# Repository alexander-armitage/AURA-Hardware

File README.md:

<div align="center">

# AURA
### Autonomous Universal Robotics Architecture

</div>

## Contents

1. [Overview](#overview)  
2. [Repository Structure](#repository-structure)
3. [License](#license)

## Overview

AURA (Autonomous Universal Robotics Architecture) is a modular set of PCBs designed for robotics applications. This repository includes schematics, layouts, and KiCad project files to facilitate prototyping and production.

The software framework to run on this hardware can be seen in another repository [here](https://github.com/alexander-armitage/AURA-Software).

### Features
#### MCU
- Dual Core 240MHz ESP32-S3
- Onboard IMU (ICM20948) 
- Onboard barometer (BMP280)
- Flash storage (128 MBit)
- SD card support
- 1x CAN connector
- 1x I2C connector
- 2x SPI connector
- 2x UART connectors
- 12x PWM output channels
- Power switching
- ESD protection

#### PDB
- 1x Battery pass-through
- 1x 5V 20A continuous output
- 2x high-current (10A) output channels
- 2S-6S LiPo battery input support
- Reverse polarity protection
- Power, Current, and Voltage sensing
- ESD protection

## Repository Structure

```
AURA-Hardware/
├── .github/              # Images for README
├── MCU_AURA/             # ESP32S3 based PCB project
│ ├── Gerber/             # Manufacturing files (JLCPCB)
│ ├── Libraries/          # Local project libraries
| ├── Pick_n_Place/       # Files to generate pick and place (JLCPCB)
│ └── MCU_AURA.kicad_pro  # Project file for KiCad
├── PDB_AURA/             # Power distribution board PCB project
│ ├── Gerber/             # Manufacturing files (JLCPCB)
│ ├── Libraries/          # Local project libraries
| ├── Pick_n_Place/       # Files to generate pick and place (JLCPCB)
│ └── PDB_AURA.kicad_pro  # Project file for KiCad
├── docs/                 # Schematics for the PCB projects
├── .gitignore            # Git ignore file
├── README.md             # Project overview
└── LICENSE               # License file
```

## License
See the [LICENSE](./LICENSE) file for more details.

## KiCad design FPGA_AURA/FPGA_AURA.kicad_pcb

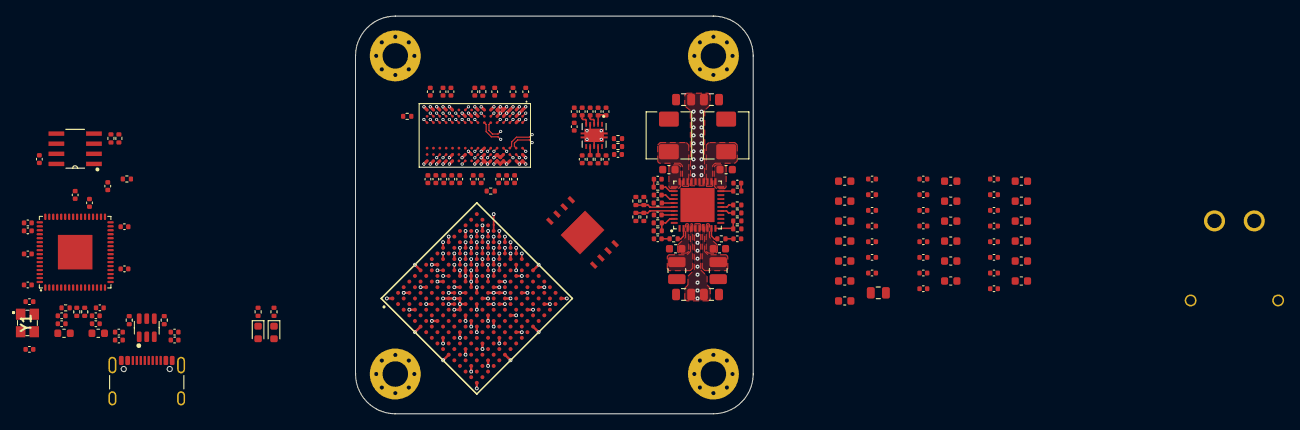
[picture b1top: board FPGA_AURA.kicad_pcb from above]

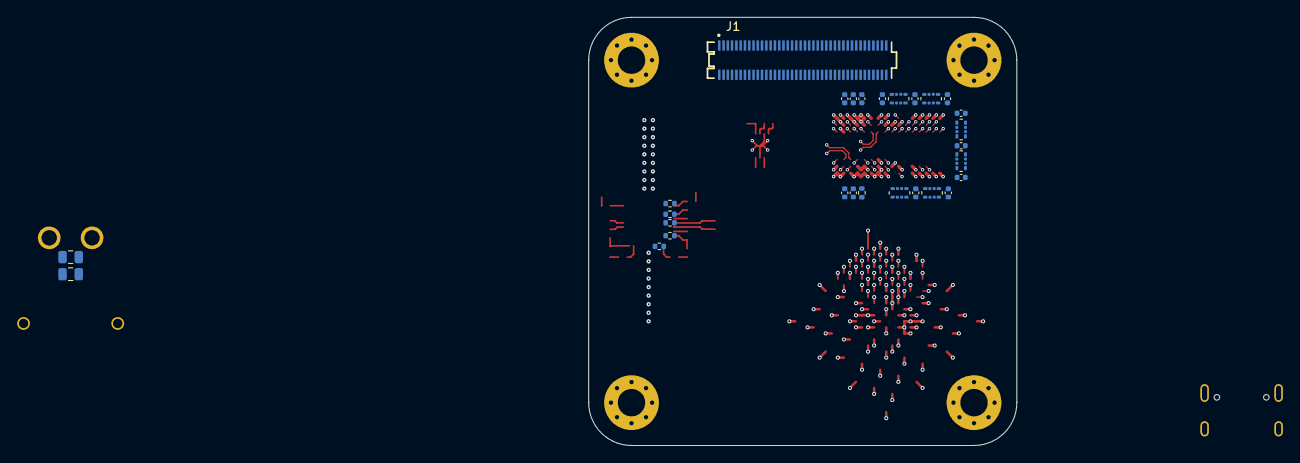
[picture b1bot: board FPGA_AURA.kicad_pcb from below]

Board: 8 copper layers, 50.0 x 50.0 mm, 187 parts (28 on the bottom side), 111 nets.

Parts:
C1, C3, C4, C5, C6, C7, C8, C9, C10, C12, C14, C17, C102, C103, C214, C500, C501, C502, C503, C504, C505, C506, C507, C512, C513, C514, C515, C516, C517, C518, C519, C520, C521, C522, C523, C524, C525, C526, C527, C528, C529, C530, C531: 100n; C_0402_1005Metric
C2, C11, C13, C221: 4u7; C_0402_1005Metric
C15, C16: 27pF; C_0402_1005Metric
C18: 100u; C_0805_2012Metric
C19, C20, C21, C22, C24, C34, C35, C41, C42, C48, C49, C55, C56: 4u7; C_0603_1608Metric
C23, C26, C27, C28, C29, C30, C31, C36, C37, C38, C39, C43, C44, C45, C46, C50, C51, C52, C53, C57, C58, C59, C60, C205: 470n; C_0402_1005Metric
C25, C32, C33, C40, C47, C54: 47; C_0603_1608Metric
C100, C101, C206, C207, C208, C209: 47u; C_0805_2012Metric
C104, C105, C220: 1u; C_0402_1005Metric
C200, C201, C202, C203: 10u; C_0603_1608Metric
C210: 3n6; C_0402_1005Metric
C211: 8n; C_0402_1005Metric
C212: 2n2; C_0402_1005Metric
C213: 5n; C_0402_1005Metric
C215, C217, C218, C219, C222, C508: 10u; C_0402_1005Metric
C216: 1n; C_0402_1005Metric
C510, C511: 10n; C_0402_1005Metric
D105, D106: LED; LED_0603_1608Metric
FB1, FB2: 120R; L_0603_1608Metric
H100, H101, H102, H103: MountingHole_Pad; MountingHole_3.2mm_M3_Pad_Via
J1: ST5-40-1.00-L-D-P-TR
J100: USB_C_Receptacle_USB2.0_16P; USB_C_Receptacle_GCT_USB4105-xx-A_16P_TopMnt_Horizontal
J101: XT30PW-M; XT30PWM
L200: 680n; L_Chilisin_BMRB00050518-B
L201: 1u; L_Chilisin_BMRB00050518-B
L202: 1u5; L_1008_2520Metric
L203: 2u2; L_1008_2520Metric
R1: 10R; R_0402_1005Metric
R2, R3: 22R; R_0402_1005Metric
R4, R108, R109, R209: 1k; R_0402_1005Metric
R5, R6: 12k; R_0402_1005Metric
R100, R101: 5k1; R_0402_1005Metric
R200: 27k; R_0402_1005Metric
R201: 4k9; R_0402_1005Metric
R202, R204: 0R; R_0402_1005Metric
R203: 56k2; R_0402_1005Metric
R205: 31k6; R_0402_1005Metric
R206: 100k; R_0402_1005Metric
R207, R208, R210, R211, R213, R220, R221, R222, R223, R524: 10k; R_0402_1005Metric
R212: 22k; R_0402_1005Metric
R214: 15k; R_0402_1005Metric
R215, R216: 2k7; R_0402_1005Metric
R217: 5k6; R_0402_1005Metric
R218: 9k1; R_0402_1005Metric
R219: 47k; R_0402_1005Metric
R508, R509, R510, R511, R512, R513: 0402_4
R522: 81R; R_0402_1005Metric
R523: 240R; R_0402_1005Metric
R525: 40R; R_0402_1005Metric
U1: XC7A35T-2FTG256C; BGA256C100P16X16_1700X1700X155
U2: W25Q256JVEIQ; SON127P800X600X80-9N
U3: FT2232HQ; QFN50P900X900X100-65N
U4: TPS51200DRCR; VREG_V62_16624-01YE
U5: USBLC6-2SC6; SOT-23-6
U6: 93LC56BT-I_SN; SOIC127P600X175-8N
U200: ADP5014; QFN50P600X600X80-41N430X430
U500: MT41K128M16JT-125_IT_K; BGA80P96C6X16_800X1400X110
Y1: 12MHz; X322512MSB4SI

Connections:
+1V0: C18.1, C19.1, C20.1, C21.1, C23.1, C26.1, C27.1, C28.1, C206.1, L200.2, U1.E10 (VCCBRAM), U1.F7 (VCCINT), U1.F9 (VCCINT), U1.F11 (VCCBRAM), U1.G6 (VCCINT), U1.H9 (VCCINT), U1.J6 (VCCINT), U1.K9 (VCCINT), U1.L8 (VCCINT), U200.33 (FB1)
+1V8: C22.1, C24.1, C25.1, C29.1, C30.1, C31.1, C207.1, L201.2, U1.G8 (VCCADC_0), U1.G10 (VCCAUX), U1.J10 (VCCAUX), U1.K11 (VCCAUX), U1.L10 (VCCAUX), U200.18 (FB2)
+1V8_FTDI: C2.1, C8.1, C9.1, C10.1, U3.12 (VCORE), U3.37 (VCORE), U3.49 (VREGOUT), U3.64 (VCORE)
+1V35: C40.1, C41.1, C42.1, C43.1, C44.1, C45.1, C46.1, C208.1, C217.1, C218.1, C511.1, C512.1, C513.1, C514.1, C515.1, C516.1, C517.1, C518.1, C519.1, C520.1, C521.1, C522.1, C523.1, C524.1, C525.1, C526.1, C527.1, C528.1, C529.1, C530.1, C531.1, L202.2, R222.1, U1.A16 (VCCO_15), U1.B13 (VCCO_15), U1.C10 (VCCO_15), U1.E14 (VCCO_15), U1.H15 (VCCO_15), U1.J12 (VCCO_15), U4.2 (VLDOIN), U200.1 (FB3), U500.A1 (VDDQ), U500.A8 (VDDQ), U500.B2 (VDD), U500.C1 (VDDQ), U500.C9 (VDDQ), U500.D2 (VDDQ), U500.D9 (VDD), U500.E9 (VDDQ), U500.F1 (VDDQ), U500.G7 (VDD), U500.H2 (VDDQ), U500.H9 (VDDQ), U500.K2 (VDD), U500.K8 (VDD), U500.N1 (VDD), U500.N9 (VDD), U500.R1 (VDD), U500.R9 (VDD)
+3V3: C1.1, C3.1, C4.1, C5.1, C6.1, C7.1, C17.1, C32.1, C33.1, C34.1, C35.1, C36.1, C37.1, C38.1, C39.1, C47.1, C48.1, C49.1, C50.1, C51.1, C52.1, C53.1, C54.1, C55.1, C56.1, C57.1, C58.1, C59.1, C60.1, C209.1, C221.1, FB1.1, FB2.1, L203.2, R5.1, R213.1, R219.1, R220.1, R223.1, U1.A6 (VCCO_35), U1.B3 (VCCO_35), U1.D7 (VCCO_35), U1.E4 (VCCO_35), U1.F1 (VCCO_35), U1.J2 (VCCO_35), U1.L6 (VCCO_0), U1.L16 (VCCO_14), U1.M3 (VCCO_34), U1.M13 (VCCO_14), U1.N10 (VCCO_14), U1.P7 (VCCO_14), U1.R4 (VCCO_34), U1.R14 (VCCO_14), U1.T1 (VCCO_34), U1.T11 (VCCO_14), U2.8 (VCC), U3.20 (VCCIO), U3.31 (VCCIO), U3.42 (VCCIO), U3.50 (VREGIN), U3.56 (VCCIO), U4.10 (VIN), U6.8 (VCC)
+5V: C100.1, C101.1, C200.1, C201.1, C202.1, C203.1, C220.1, D106.2 (A), J101.1, R200.1, U200.3 (PVIN3), U200.8 (PVIN4), U200.17 (EN1/ENALL), U200.20 (PVIN2), U200.21 (PVIN2), U200.30 (PVIN1), U200.31 (PVIN1), U200.34 (AVIN)
+5V_USB: C102.1, C103.1, C104.1, C105.1, D105.2 (A), J100.A4 (VBUS), J100.A9 (VBUS), J100.B4 (VBUS), J100.B9 (VBUS), U5.5 (VBUS)
+VREF: C205.1, C214.1, C510.1, C511.2, R207.1, R209.1, R211.1, U4.6 (REFOUT), U200.38 (VREF), U200.40 (VSET4), U500.H1 (VREFDQ), U500.M8 (VREFCA)
+VTT: C215.1, C219.1, C222.1, C500.1, C501.1, C502.1, C503.1, C504.1, C505.1, C506.1, C507.1, C508.1, R508.1, R508.3, R508.5, R508.7, R509.1, R509.3, R509.5, R509.7, R510.1, R510.3, R510.5, R510.7, R511.1, R511.3, R511.5, R511.7, R512.1, R512.3, R512.5, R512.7, R513.3, R513.5, R525.1, U4.3 (VO), U4.5 (VOSNS)
/100_Power_Switching/5V_LED: D106.1 (K), R109.2
/100_Power_Switching/USB_CC1: J100.A5 (CC1), R101.2
/100_Power_Switching/USB_CC2: J100.B5 (CC2), R100.2
/100_Power_Switching/USB_LED: D105.1 (K), R108.2
/200_Power_Regulation/ADP_1V0_PD: R207.2, R208.1, U200.36 (VSET1)
/200_Power_Regulation/ADP_1V8_PD: R209.2, R210.1, U200.37 (VSET2)
/200_Power_Regulation/ADP_1V35_PD: R211.2, R212.1, U200.39 (VSET3)
/200_Power_Regulation/ADP_CFG1: R204.1, U200.15 (CFG1)
/200_Power_Regulation/ADP_CFG2: R205.1, U200.14 (CFG2)
/200_Power_Regulation/ADP_COMP1: R215.1, U200.32 (COMP1)
/200_Power_Regulation/ADP_COMP2: R216.1, U200.19 (COMP2)
/200_Power_Regulation/ADP_COMP3: R217.1, U200.2 (COMP3)
/200_Power_Regulation/ADP_COMP4: R218.1, U200.9 (COMP4)
/200_Power_Regulation/ADP_EN2: R202.2, U200.16 (EN2/DL12)
/200_Power_Regulation/ADP_EN4: R203.2, U200.12 (EN4/DL34)
/200_Power_Regulation/ADP_FB4: R213.2, R214.1, U200.10 (FB4)
/200_Power_Regulation/ADP_RC1: C210.1, R215.2
/200_Power_Regulation/ADP_RC2: C211.1, R216.2
/200_Power_Regulation/ADP_RC3: C212.1, R217.2
/200_Power_Regulation/ADP_RC4: C213.1, R218.2
/200_Power_Regulation/ADP_RT: R206.1, U200.35 (RT)
/200_Power_Regulation/ADP_SW1: L200.1, U200.28 (SW1), U200.29 (SW1)
/200_Power_Regulation/ADP_SW2: L201.1, U200.22 (SW2), U200.23 (SW2)
/200_Power_Regulation/ADP_SW3: L202.1, U200.4 (SW3)
/200_Power_Regulation/ADP_SW4: L203.1, U200.7 (SW4)
/200_Power_Regulation/ADP_UV: R200.2, R201.1, U200.13 (EN3/UV)
/200_Power_Regulation/TPS_REFIN: C216.1, R221.1, R222.2, U4.1 (REFIN)
/400_FPGA_Config/FTDI_EECLK: U3.62 (EECLK), U6.2 (CLK)
/400_FPGA_Config/FTDI_EECS: U3.63 (EECS), U6.1 (CS)
/400_FPGA_Config/FTDI_EEDI: R4.2, U3.61 (EEDATA), U6.3 (DI)
/400_FPGA_Config/FTDI_EEDO: R4.1, R5.2, U6.4 (DO)
/400_FPGA_Config/FTDI_REF: R6.1, U3.6 (REF)
/400_FPGA_Config/OSCI_FTDI: C15.1, U3.2 (OSCI), Y1.1
/400_FPGA_Config/OSCO_FTDI: C16.1, U3.3 (OSCO), Y1.3
/400_FPGA_Config/QSPI_CLK: R1.2, U2.6 (CLK)
/400_FPGA_Config/QSPI_CLK_R: R1.1, U1.E8 (CCLK_0)
/400_FPGA_Config/QSPI_CS#: U1.L12 (IO_L6P_T0_FCS_B_14), U2.1 (/CS)
/400_FPGA_Config/QSPI_IO0: U1.J13 (IO_L1P_T0_D00_MOSI_14), U2.5 (DI_IO0)
/400_FPGA_Config/QSPI_IO1: U1.J14 (IO_L1N_T0_D01_DIN_14), U2.2 (DO_IO1)
/400_FPGA_Config/QSPI_IO2: U1.K15 (IO_L2P_T0_D02_14), U2.3 (/WP_IO2)
/400_FPGA_Config/QSPI_IO3: U1.K16 (IO_L2N_T0_D03_14), U2.7 (/HOLD_IO3)
/400_FPGA_Config/USB_FPGA_D+: R2.1, U5.4 (I/O2)
/400_FPGA_Config/USB_FPGA_D-: R3.1, U5.6 (I/O1)
/400_FPGA_Config/USB_R_D+: R2.2, U3.8 (DP)
/400_FPGA_Config/USB_R_D-: R3.2, U3.7 (DM)
/400_FPGA_Config/VPHY_FTDI: C13.1, C14.1, FB2.2, U3.4 (VPHY)
/400_FPGA_Config/VPLL_FTDI: C11.1, C12.1, FB1.2, U3.9 (VPLL)
/500_DDR3L/DDR3_ZQ: R523.1, U500.L8 (ZQ)
ADP_UVO_LED: R219.2, U200.11 (GPIO)
DDR3_A0: R509.8, U1.B11 (IO_L4N_T0_15), U500.N3 (A0)
DDR3_A1: R509.6, U1.B16 (IO_L10N_T1_AD11N_15), U500.P7 (A1)
DDR3_A2: R509.4, U1.C13 (IO_L12N_T1_MRCC_15), U500.P3 (A2)
DDR3_A3: R509.2, U1.B12 (IO_L5P_T0_AD9P_15), U500.N2 (A3)
DDR3_A4: R508.8, U1.B10 (IO_L4P_T0_15), U500.P8 (A4)
DDR3_A5: R508.6, U1.D8 (IO_L6P_T0_15), U500.P2 (A5)
DDR3_A6: R508.4, U1.C9 (IO_L1N_T0_AD0N_15), U500.R8 (A6)
DDR3_A7: R508.2, U1.C8 (IO_L1P_T0_AD0P_15), U500.R2 (A7)
DDR3_A8: R512.8, U1.A9 (IO_L2N_T0_AD8N_15), U500.T8 (A8)
DDR3_A9: R512.6, U1.D9 (IO_L6N_T0_VREF_15), U500.R3 (A9)
DDR3_A10: R512.4, U1.A14 (IO_L7N_T1_AD2N_15), U500.L7 (A10/AP)
DDR3_A11: R512.2, U1.A8 (IO_L2P_T0_AD8P_15), U500.R7 (A11)
DDR3_A12: R513.6, U1.A15 (IO_L9N_T1_DQS_AD3N_15), U500.N7 (A12/~BC)
DDR3_A13: R513.4, U1.D10 (IO_0_15), U500.T3 (A13)
DDR3_BA0: R510.2, U1.C12 (IO_L11N_T1_SRCC_15), U500.M2 (BA0)
DDR3_BA1: R510.4, U1.A12 (IO_L5N_T0_AD9N_15), U500.N8 (BA1)
DDR3_BA2: R510.6, U1.A13 (IO_L7P_T1_AD2P_15), U500.M3 (BA2)
DDR3_CAS: R511.6, U1.B14 (IO_L8N_T1_AD10N_15), U500.K3 (~CAS)
DDR3_CK+: R522.1, U1.B9 (IO_L3P_T0_DQS_AD1P_15), U500.J7 (CK)
DDR3_CK-: R522.2, U1.A10 (IO_L3N_T0_DQS_AD1N_15), U500.K7 (~CK)
DDR3_CKE: R510.8, U1.C11 (IO_L11P_T1_SRCC_15), U500.K9 (CKE)
DDR3_CS: R511.2, U1.B15 (IO_L9P_T1_DQS_AD3P_15), U500.L2 (~CS)
DDR3_DM0: U1.E13 (IO_L13N_T2_MRCC_15), U500.E7 (LDM)
DDR3_DM1: U1.H11 (IO_L19P_T3_A22_15), U500.D3 (UDM)
DDR3_DQ0: U1.E11 (IO_L14P_T2_SRCC_15), U500.E3 (DQ0)
DDR3_DQ1: U1.D11 (IO_L14N_T2_SRCC_15), U500.F7 (DQ1)
DDR3_DQ2: U1.F12 (IO_L16P_T2_A28_15), U500.F2 (DQ2)
DDR3_DQ3: U1.D16 (IO_L17N_T2_A25_15), U500.F8 (DQ3)
DDR3_DQ4: U1.F15 (IO_L18P_T2_A24_15), U500.H3 (DQ4)
DDR3_DQ5: U1.E15 (IO_L18N_T2_A23_15), U500.H8 (DQ5)
DDR3_DQ6: U1.F13 (IO_L16N_T2_A27_15), U500.G2 (DQ6)
DDR3_DQ7: U1.E16 (IO_L17P_T2_A26_15), U500.H7 (DQ7)
DDR3_DQ8: U1.H13 (IO_L20N_T3_A19_15), U500.A7 (DQ12)
DDR3_DQ9: U1.G15 (IO_L24N_T3_RS0_15), U500.C3 (DQ9)
DDR3_DQ10: U1.G12 (IO_L19N_T3_A21_VREF_15), U500.C8 (DQ10)
DDR3_DQ11: U1.H12 (IO_L20P_T3_A20_15), U500.D7 (DQ8)
DDR3_DQ12: U1.J16 (IO_L23N_T3_FWE_B_15), U500.C2 (DQ11)
DDR3_DQ13: U1.J15 (IO_L23P_T3_FOE_B_15), U500.A2 (DQ13)
DDR3_DQ14: U1.G16 (IO_L22N_T3_A16_15), U500.B8 (DQ14)
DDR3_DQ15: U1.H16 (IO_L22P_T3_A17_15), U500.A3 (DQ15)
DDR3_DQS0+: U1.D14 (IO_L15P_T2_DQS_15), U500.F3 (LDQS)
DDR3_DQS0-: U1.D15 (IO_L15N_T2_DQS_ADV_B_15), U500.G3 (~LDQS)
DDR3_DQS1+: U1.G14 (IO_L21P_T3_DQS_15), U500.C7 (UDQS)
DDR3_DQS1-: U1.F14 (IO_L21N_T3_DQS_A18_15), U500.B7 (~UDQS)
DDR3_ODT: R525.2, U1.C16 (IO_L10P_T1_AD11P_15), U500.K1 (ODT)
DDR3_RAS: R511.4, U1.C14 (IO_L8P_T1_AD10P_15), U500.J3 (~RAS)
DDR3_RESET: R524.1, U1.E12 (IO_L13P_T2_MRCC_15), U500.T2 (~RESET)
DDR3_WE: R511.8, U1.D13 (IO_L12P_T1_MRCC_15), U500.L3 (~WE)
DDR_PGOOD: R223.2, U4.9 (PGOOD)
GND: C1.2, C2.2, C3.2, C4.2, C5.2, C6.2, C7.2, C8.2, C9.2, C10.2, C11.2, C12.2, C13.2, C14.2, C15.2, C16.2, C17.2, C18.2, C19.2, C20.2, C21.2, C22.2, C23.2, C24.2, C25.2, C26.2, C27.2, C28.2, C29.2, C30.2, C31.2, C32.2, C33.2, C34.2, C35.2, C36.2, C37.2, C38.2, C39.2, C40.2, C41.2, C42.2, C43.2, C44.2, C45.2, C46.2, C47.2, C48.2, C49.2, C50.2, C51.2, C52.2, C53.2, C54.2, C55.2, C56.2, C57.2, C58.2, C59.2, C60.2, C100.2, C101.2, C102.2, C103.2, C104.2, C105.2, C200.2, C201.2, C202.2, C203.2, C205.2, C206.2, C207.2, C208.2, C209.2, C210.2, C211.2, C212.2, C213.2, C214.2, C215.2, C216.2, C217.2, C218.2, C219.2, C220.2, C221.2, C222.2, C500.2, C501.2, C502.2, C503.2, C504.2, C505.2, C506.2, C507.2, C508.2, C510.2, C512.2, C513.2, C514.2, C515.2, C516.2, C517.2, C518.2, C519.2, C520.2, C521.2, C522.2, C523.2, C524.2, C525.2, C526.2, C527.2, C528.2, C529.2, C530.2, C531.2, H100.1 (1_1), H101.1 (1_1), H102.1 (1_1), H103.1 (1_1), J100.A1 (GND), J100.A12 (GND), J100.B1 (GND), J100.B12 (GND), J101.2, J101.3, J101.4, R6.2, R100.1, R101.1, R108.1, R109.1, R201.2, R202.1, R203.1, R204.2, R205.2, R206.2, R208.2, R210.2, R212.2, R214.2, R221.2, R523.2, R524.2, U1.A1 (GND), U1.A11 (GND), U1.B8 (GND), U1.C5 (GND), U1.C15 (GND), U1.D2 (GND), U1.D12 (GND), U1.E9 (GND), U1.F6 (GND), U1.F8 (VCCBATT_0), U1.F10 (GND), U1.F16 (GND), U1.G3 (GND), U1.G7 (GNDADC_0), U1.G9 (GND), U1.G13 (GND), U1.H6 (GND), U1.H7 (VREFN_0), U1.J8 (VREFP_0), U1.J9 (GND), U1.J11 (GND), U1.K4 (GND), U1.K6 (GND), U1.K14 (GND), U1.L1 (GND), U1.L11 (GND), U1.M8 (GND), U1.N5 (GND), U1.N15 (GND), U1.P2 (GND), U1.P12 (GND), U1.R9 (GND), U1.T6 (GND), U1.T16 (GND), U2.4 (GND), U2.9 (EXP), U3.1 (GND), U3.5 (GND), U3.10 (AGND), U3.11 (GND), U3.13 (TEST), U3.15 (GND), U3.25 (GND), U3.35 (GND), U3.47 (GND), U3.51 (GND), U3.65 (GND), U4.4 (PGND), U4.8 (GND), U4.11 (EPAD), U5.2 (GND), U6.5 (VSS), U200.5 (PGND3), U200.6 (PGND4), U200.24 (PGND2), U200.25 (PGND2), U200.26 (PGND1), U200.27 (PGND1), U200.41 (EP), U500.A9 (VSS), U500.B1 (VSSQ), U500.B3 (VSS), U500.B9 (VSSQ), U500.D1 (VSSQ), U500.D8 (VSSQ), U500.E1 (VSS), U500.E2 (VSSQ), U500.E8 (VSSQ), U500.F9 (VSSQ), U500.G1 (VSSQ), U500.G8 (VSS), U500.G9 (VSSQ), U500.J2 (VSS), U500.J8 (VSS), U500.M1 (VSS), U500.M9 (VSS), U500.P1 (VSS), U500.P9 (VSS), U500.T1 (VSS), U500.T9 (VSS), Y1.2, Y1.4
unnamed: R220.2, U4.7 (EN)
USB_D+: J100.A6 (D+), J100.B6 (D+), U5.3 (I/O2)
USB_D-: J100.A7 (D-), J100.B7 (D-), U5.1 (I/O1)

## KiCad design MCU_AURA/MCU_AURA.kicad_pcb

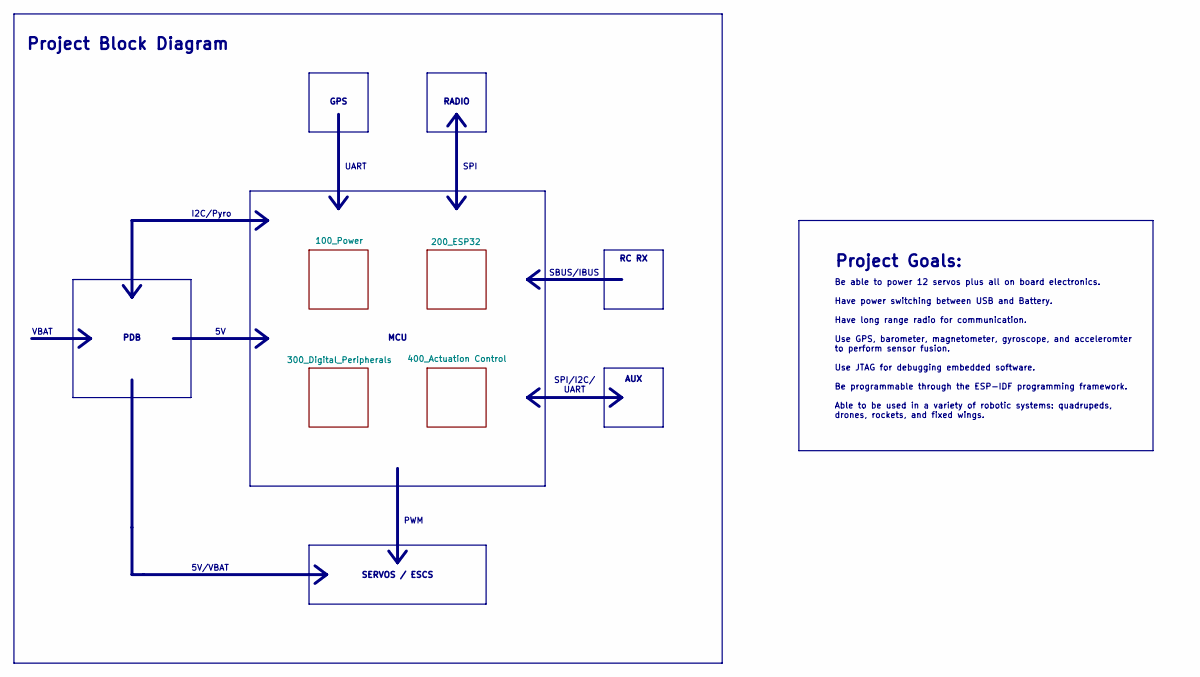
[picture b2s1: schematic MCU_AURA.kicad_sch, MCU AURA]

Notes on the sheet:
GPS
SPI
SPI/I2C/ UART
UART
Be able to power 12 servos plus all on board electronics. Have power switching between USB and Battery. Have long range radio for communication. Use GPS, barometer, magnetometer, gyroscope, and acceleromter to perform sensor fusion. Use JTAG for debugging embedded software. Be programmable through 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
SBUS/IBUS
RADIO
PDB
I2C/Pyro
Project Block Diagram
MCU
Project Goals:
5V/VBAT
PWM
VBAT
AUX
RC RX
SERVOS / ESCS

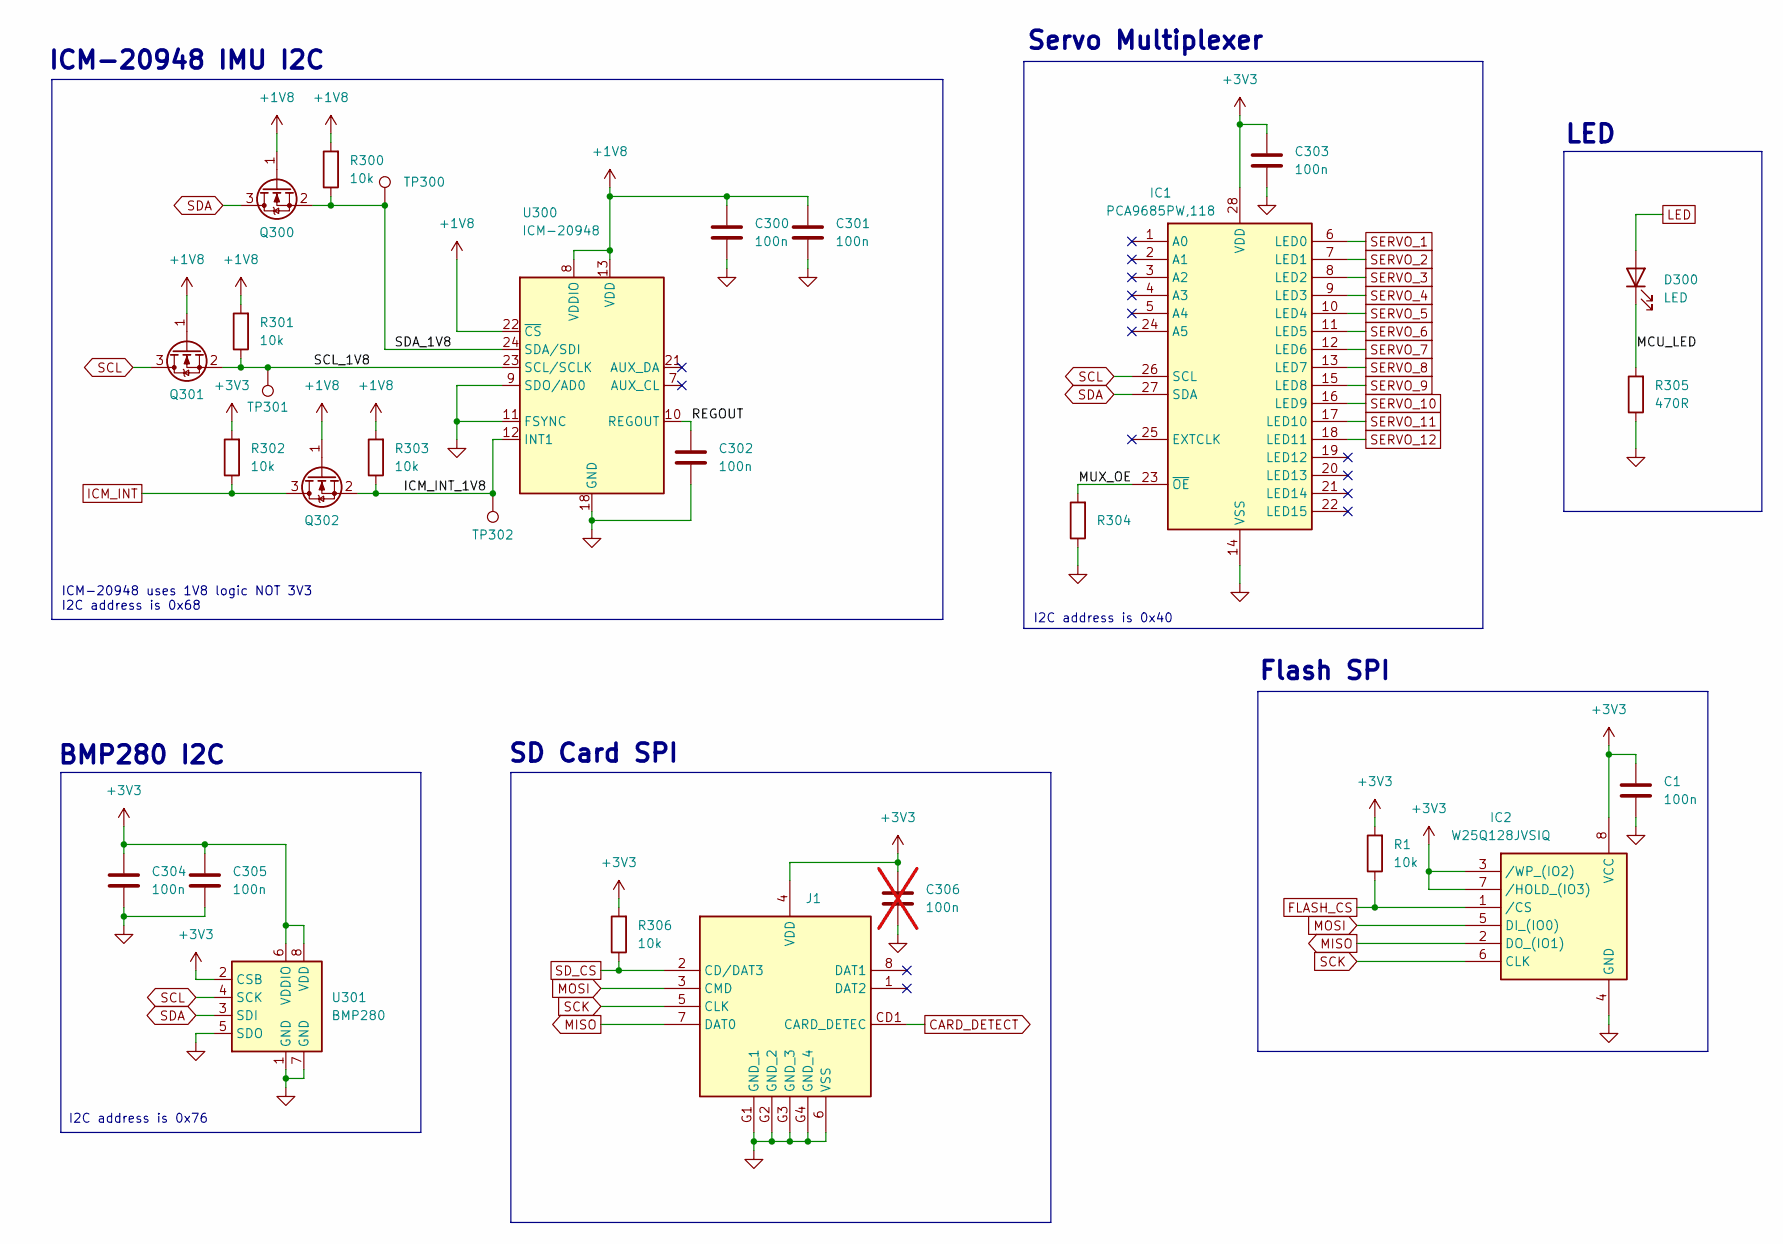
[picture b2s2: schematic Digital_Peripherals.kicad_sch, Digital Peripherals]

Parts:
C1, C300, C301, C302, C303, C304, C305: 100n; C_0402_1005Metric
C306: 100n; C_0402_1005Metric; not fitted
D300: LED; LED_0603_1608Metric
IC1: PCA9685PW,118; SOP65P640X110-28N; Manufacturer_Part_Number PCA9685PW,118; Mouser Part Number 771-PCA9685PW,118
IC2: W25Q128JVSIQ; SOIC127P790X216-8N; Manufacturer_Part_Number W25Q128JVSIQ; Mouser Part Number 454-W25Q128JVSIQ
J1: TF-CARD_H1.8; TFCARDH18; Manufacturer_Part_Number TF-CARD H1.8
Q300, Q301, Q302: BSS138; SOT-23
R1, R300, R301, R302, R303, R304, R306: 10k; R_0402_1005Metric
R305: 470R; R_0402_1005Metric
TP300, TP301, TP302: TestPoint; TestPoint_Pad_D1.0mm
U300: ICM-20948; InvenSense_QFN-24_3x3mm_P0.4mm
U301: BMP280; Bosch_LGA-8_2x2.5mm_P0.65mm_ClockwisePinNumbering

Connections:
+1V8: C300.1, C301.1, Q300.1 (G), Q301.1 (G), Q302.1 (G), R300.2, R301.2, R303.2, U300.8 (VDDIO), U300.13 (VDD), U300.22 (~CS); also elsewhere on the board
+3V3: C1.1, C303.1, C304.1, C305.1, C306.1, IC1.28 (VDD), IC2.3 (/WP_(IO2)), IC2.7 (/HOLD_(IO3)), IC2.8 (VCC), J1.4 (VDD), R1.2, R302.2, R306.2, U301.2 (CSB), U301.6 (VDDIO), U301.8 (VDD); also elsewhere on the board
/300_Digital_Peripherals/ICM_INT_1V8: Q302.2 (S), R303.1, TP302.1, U300.12 (INT1)
/300_Digital_Peripherals/MCU_LED: D300.1 (K), R305.2
/300_Digital_Peripherals/MUX_OE: IC1.23 (~OE), R304.2
/300_Digital_Peripherals/REGOUT: C302.1, U300.10 (REGOUT)
/300_Digital_Peripherals/SCL_1V8: Q301.2 (S), R301.1, TP301.1, U300.23 (SCL/SCLK)
/300_Digital_Peripherals/SDA_1V8: Q300.2 (S), R300.1, TP300.1, U300.24 (SDA/SDI)
CARD_DETECT: J1.CD1 (CARD_DETEC); also elsewhere on the board
FLASH_CS: IC2.1 (/CS), R1.1; also elsewhere on the board
GND: C1.2, C300.2, C301.2, C302.2, C303.2, C304.2, C305.2, C306.2, IC1.14 (VSS), IC2.4 (GND), J1.6 (VSS), J1.G1 (GND_1), J1.G2 (GND_2), J1.G3 (GND_3), J1.G4 (GND_4), R304.1, R305.1, U300.9 (SDO/AD0), U300.11 (FSYNC), U300.18 (GND), U300.20 (GND), U301.1 (GND), U301.5 (SDO), U301.7 (GND); also elsewhere on the board
ICM_INT: Q302.3 (D), R302.1; also elsewhere on the board
LED: D300.2 (A); also elsewhere on the board
MISO: IC2.2 (DO_(IO1)), J1.7 (DAT0); also elsewhere on the board
MOSI: IC2.5 (DI_(IO0)), J1.3 (CMD); also elsewhere on the board
SCK: IC2.6 (CLK), J1.5 (CLK); also elsewhere on the board
SCL: IC1.26 (SCL), Q301.3 (D), U301.4 (SCK); also elsewhere on the board
SDA: IC1.27 (SDA), Q300.3 (D), U301.3 (SDI); also elsewhere on the board
SD_CS: J1.2 (CD/DAT3), R306.1; also elsewhere on the board
SERVO_1: IC1.6 (LED0); also elsewhere on the board
SERVO_2: IC1.7 (LED1); also elsewhere on the board
SERVO_3: IC1.8 (LED2); also elsewhere on the board
SERVO_4: IC1.9 (LED3); also elsewhere on the board
SERVO_5: IC1.10 (LED4); also elsewhere on the board
SERVO_6: IC1.11 (LED5); also elsewhere on the board
SERVO_7: IC1.12 (LED6); also elsewhere on the board
SERVO_8: IC1.13 (LED7); also elsewhere on the board
SERVO_9: IC1.15 (LED8); also elsewhere on the board
SERVO_10: IC1.16 (LED9); also elsewhere on the board
SERVO_11: IC1.17 (LED10); also elsewhere on the board
SERVO_12: IC1.18 (LED11); also elsewhere on the board

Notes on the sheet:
Flash SPI
I2C address is 0x40
I2C address is 0x76
BMP280 I2C
SD Card SPI
ICM-20948 IMU I2C
Servo Multiplexer
ICM-20948 uses 1V8 logic NOT 3V3 I2C address is 0x68
LED

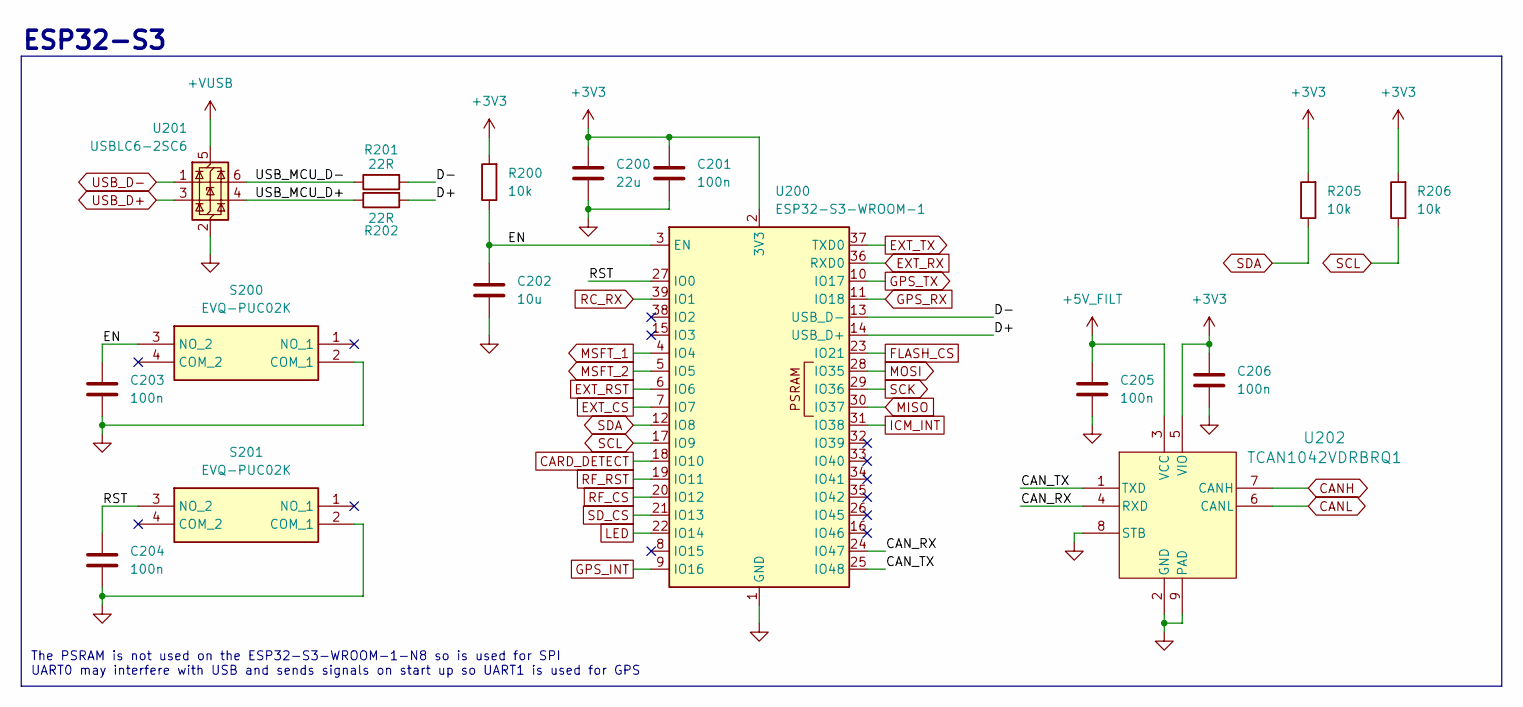
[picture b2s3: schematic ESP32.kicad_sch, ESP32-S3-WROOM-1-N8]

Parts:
C200: 22u; C_0402_1005Metric
C201, C203, C204, C205, C206: 100n; C_0402_1005Metric
C202: 10u; C_0402_1005Metric
R200, R205, R206: 10k; R_0402_1005Metric
R201, R202: 22R; R_0402_1005Metric
S200, S201: EVQ-PUC02K; EVQPUC02K; Manufacturer_Part_Number EVQ-PUC02K; Mouser Part Number 667-EVQ-PUC02K
U200: ESP32-S3-WROOM-1
U201: USBLC6-2SC6; SOT-23-6
U202: TCAN1042VDRBRQ1; DRB0008F

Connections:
+3V3: C200.1, C201.1, C206.1, R200.2, R205.2, R206.2, U200.2 (3V3), U202.5 (VIO); also elsewhere on the board
+5V_FILT: C205.1, U202.3 (VCC); also elsewhere on the board
+VUSB: U201.5 (VBUS); also elsewhere on the board
/200_ESP32/CAN_RX: U200.24 (IO47), U202.4 (RXD)
/200_ESP32/CAN_TX: U200.25 (IO48), U202.1 (TXD)
/200_ESP32/D+: R202.2, U200.14 (USB_D+)
/200_ESP32/D-: R201.2, U200.13 (USB_D-)
/200_ESP32/EN: C202.1, C203.1, R200.1, S200.3 (NO_2), U200.3 (EN)
/200_ESP32/RST: C204.1, S201.3 (NO_2), U200.27 (IO0)
/200_ESP32/USB_MCU_D+: R202.1, U201.4 (I/O2)
/200_ESP32/USB_MCU_D-: R201.1, U201.6 (I/O1)
CANH: U202.7 (CANH); also elsewhere on the board
CANL: U202.6 (CANL); also elsewhere on the board
CARD_DETECT: U200.18 (IO10); also elsewhere on the board
EXT_CS: U200.7 (IO7); also elsewhere on the board
EXT_RST: U200.6 (IO6); also elsewhere on the board
EXT_RX: U200.36 (RXD0); also elsewhere on the board
EXT_TX: U200.37 (TXD0); also elsewhere on the board
FLASH_CS: U200.23 (IO21); also elsewhere on the board
GND: C200.2, C201.2, C202.2, C203.2, C204.2, C205.2, C206.2, S200.2 (COM_1), S201.2 (COM_1), U200.1 (GND), U200.40 (GND), U200.41 (GND), U201.2 (GND), U202.2 (GND), U202.8 (STB), U202.9 (PAD); also elsewhere on the board
GPS_INT: U200.9 (IO16); also elsewhere on the board
GPS_RX: U200.11 (IO18); also elsewhere on the board
GPS_TX: U200.10 (IO17); also elsewhere on the board
ICM_INT: U200.31 (IO38); also elsewhere on the board
LED: U200.22 (IO14); also elsewhere on the board
MISO: U200.30 (IO37); also elsewhere on the board
MOSI: U200.28 (IO35); also elsewhere on the board
MSFT_1: U200.4 (IO4); also elsewhere on the board
MSFT_2: U200.5 (IO5); also elsewhere on the board
RC_RX: U200.39 (IO1); also elsewhere on the board
RF_CS: U200.20 (IO12); also elsewhere on the board
RF_RST: U200.19 (IO11); also elsewhere on the board
SCK: U200.29 (IO36); also elsewhere on the board
SCL: R206.1, U200.17 (IO9); also elsewhere on the board
SDA: R205.1, U200.12 (IO8); also elsewhere on the board
SD_CS: U200.21 (IO13); also elsewhere on the board
USB_D+: U201.3 (I/O2); also elsewhere on the board
USB_D-: U201.1 (I/O1); also elsewhere on the board

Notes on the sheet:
The PSRAM is not used on the ESP32-S3-WROOM-1-N8 so is used for SPI UART0 may interfere with USB and sends signals on start up so UART1 is used for GPS
ESP32-S3

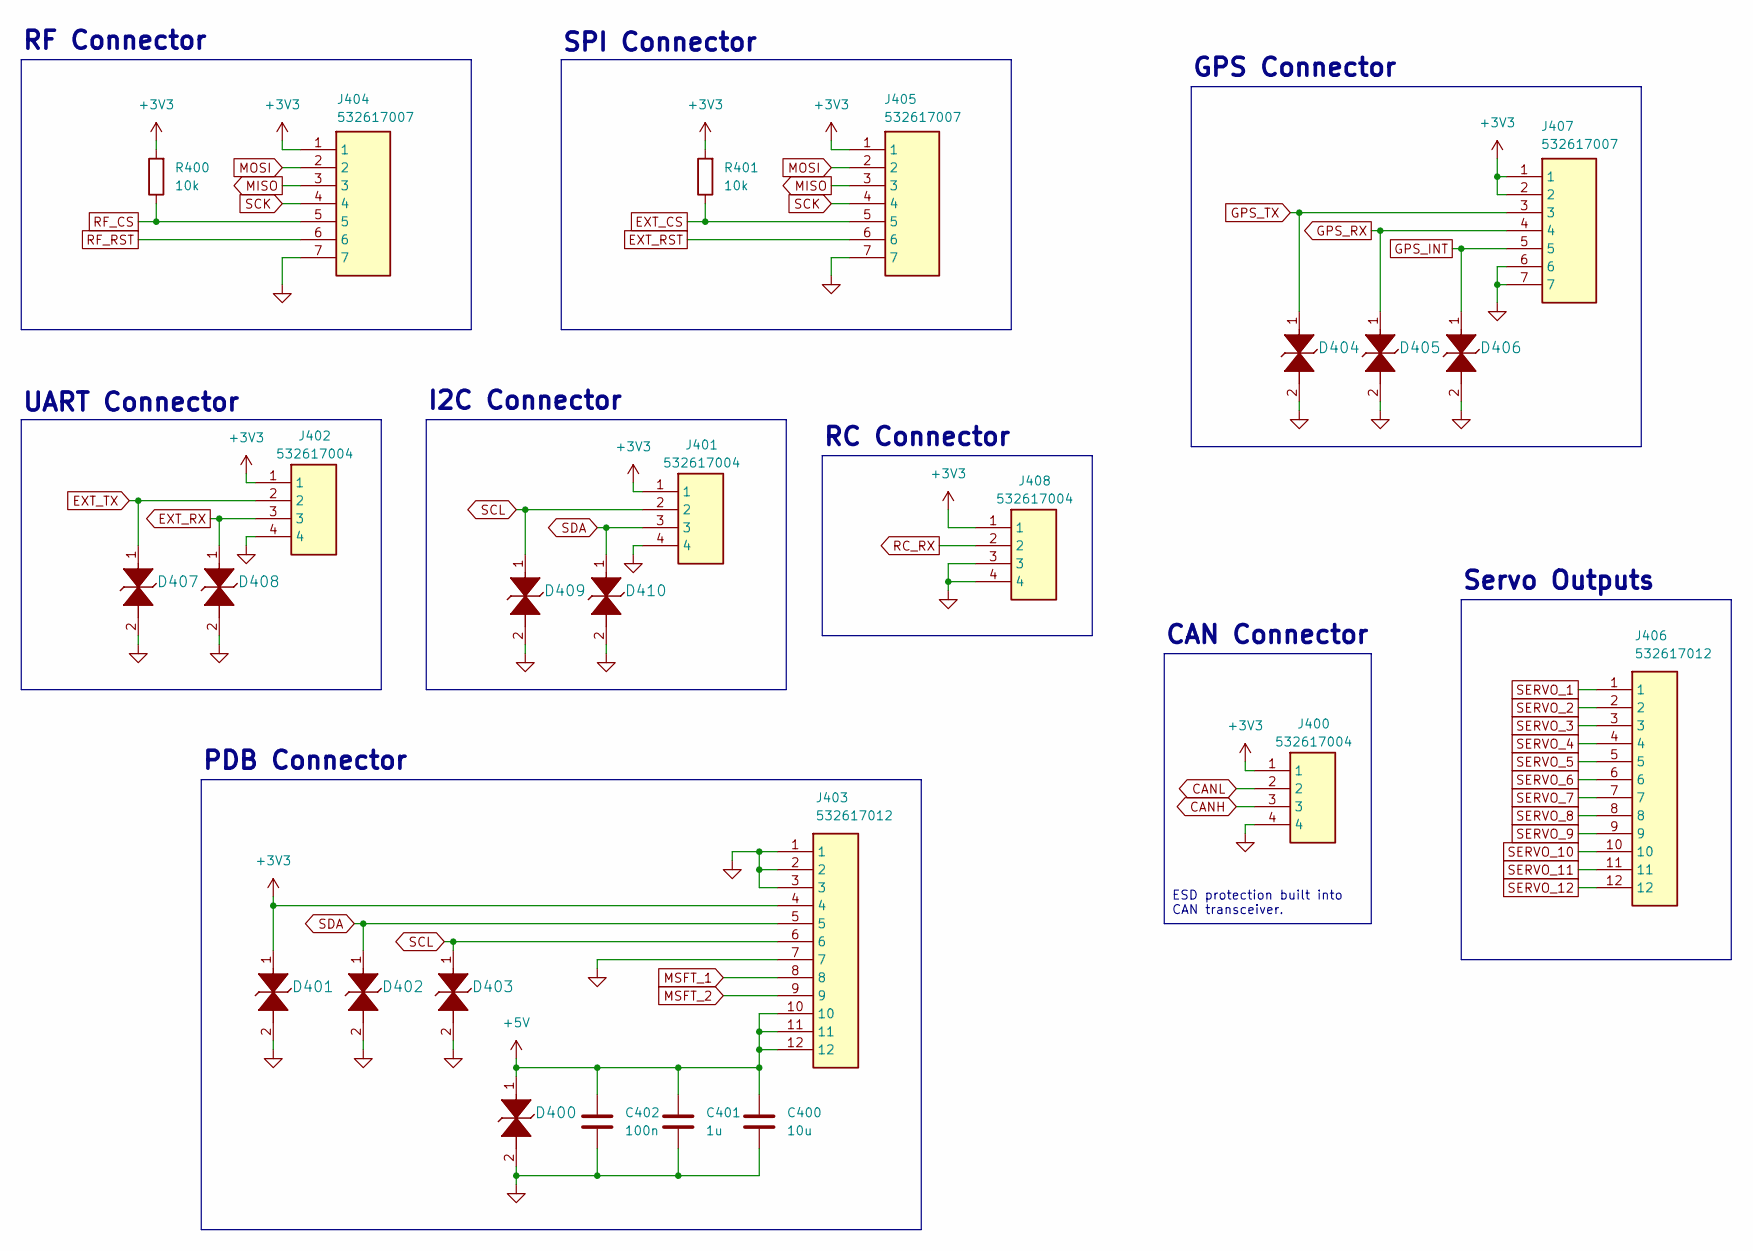
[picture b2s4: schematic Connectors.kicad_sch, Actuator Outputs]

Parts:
C400: 10u; C_0402_1005Metric
C401: 1u; C_0402_1005Metric
C402: 100n; C_0402_1005Metric
D400, D401, D402, D403, D404, D405, D406, D407, D408, D409, D410: TPD1E05U06DPYR; DIO_TPD1E05U06DPYR
J400, J401, J402, J408: 532617004; 53261-0471; Manufacturer_Part_Number 532617004
J403, J406: 532617012; 53261-1271; Manufacturer_Part_Number 532617012
J404, J405, J407: 532617007; 532610771; Manufacturer_Part_Number 532617007
R400, R401: 10k; R_0402_1005Metric

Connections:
+3V3: D401.1, J400.1, J401.1, J402.1, J403.4, J404.1, J405.1, J407.1, J407.2, J408.1, R400.2, R401.2; also elsewhere on the board
+5V: C400.1, C401.1, C402.1, D400.1, J403.10, J403.11, J403.12; also elsewhere on the board
CANH: J400.3; also elsewhere on the board
CANL: J400.2; also elsewhere on the board
EXT_CS: J405.5, R401.1; also elsewhere on the board
EXT_RST: J405.6; also elsewhere on the board
EXT_RX: D408.1, J402.3; also elsewhere on the board
EXT_TX: D407.1, J402.2; also elsewhere on the board
GND: C400.2, C401.2, C402.2, D400.2, D401.2, D402.2, D403.2, D404.2, D405.2, D406.2, D407.2, D408.2, D409.2, D410.2, J400.4, J401.4, J402.4, J403.1, J403.2, J403.3, J403.7, J404.7, J405.7, J407.6, J407.7, J408.3, J408.4; also elsewhere on the board
GPS_INT: D406.1, J407.5; also elsewhere on the board
GPS_RX: D405.1, J407.4; also elsewhere on the board
GPS_TX: D404.1, J407.3; also elsewhere on the board
MISO: J404.3, J405.3; also elsewhere on the board
MOSI: J404.2, J405.2; also elsewhere on the board
MSFT_1: J403.8; also elsewhere on the board
MSFT_2: J403.9; also elsewhere on the board
RC_RX: J408.2; also elsewhere on the board
RF_CS: J404.5, R400.1; also elsewhere on the board
RF_RST: J404.6; also elsewhere on the board
SCK: J404.4, J405.4; also elsewhere on the board
SCL: D403.1, D409.1, J401.2, J403.6; also elsewhere on the board
SDA: D402.1, D410.1, J401.3, J403.5; also elsewhere on the board
SERVO_1: J406.1; also elsewhere on the board
SERVO_2: J406.2; also elsewhere on the board
SERVO_3: J406.3; also elsewhere on the board
SERVO_4: J406.4; also elsewhere on the board
SERVO_5: J406.5; also elsewhere on the board
SERVO_6: J406.6; also elsewhere on the board
SERVO_7: J406.7; also elsewhere on the board
SERVO_8: J406.8; also elsewhere on the board
SERVO_9: J406.9; also elsewhere on the board
SERVO_10: J406.10; also elsewhere on the board
SERVO_11: J406.11; also elsewhere on the board
SERVO_12: J406.12; also elsewhere on the board

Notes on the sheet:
I2C Connector
GPS Connector
RC Connector
SPI Connector
ESD protection built into CAN transceiver.
RF Connector
Servo Outputs
PDB Connector
UART Connector
CAN Connector
